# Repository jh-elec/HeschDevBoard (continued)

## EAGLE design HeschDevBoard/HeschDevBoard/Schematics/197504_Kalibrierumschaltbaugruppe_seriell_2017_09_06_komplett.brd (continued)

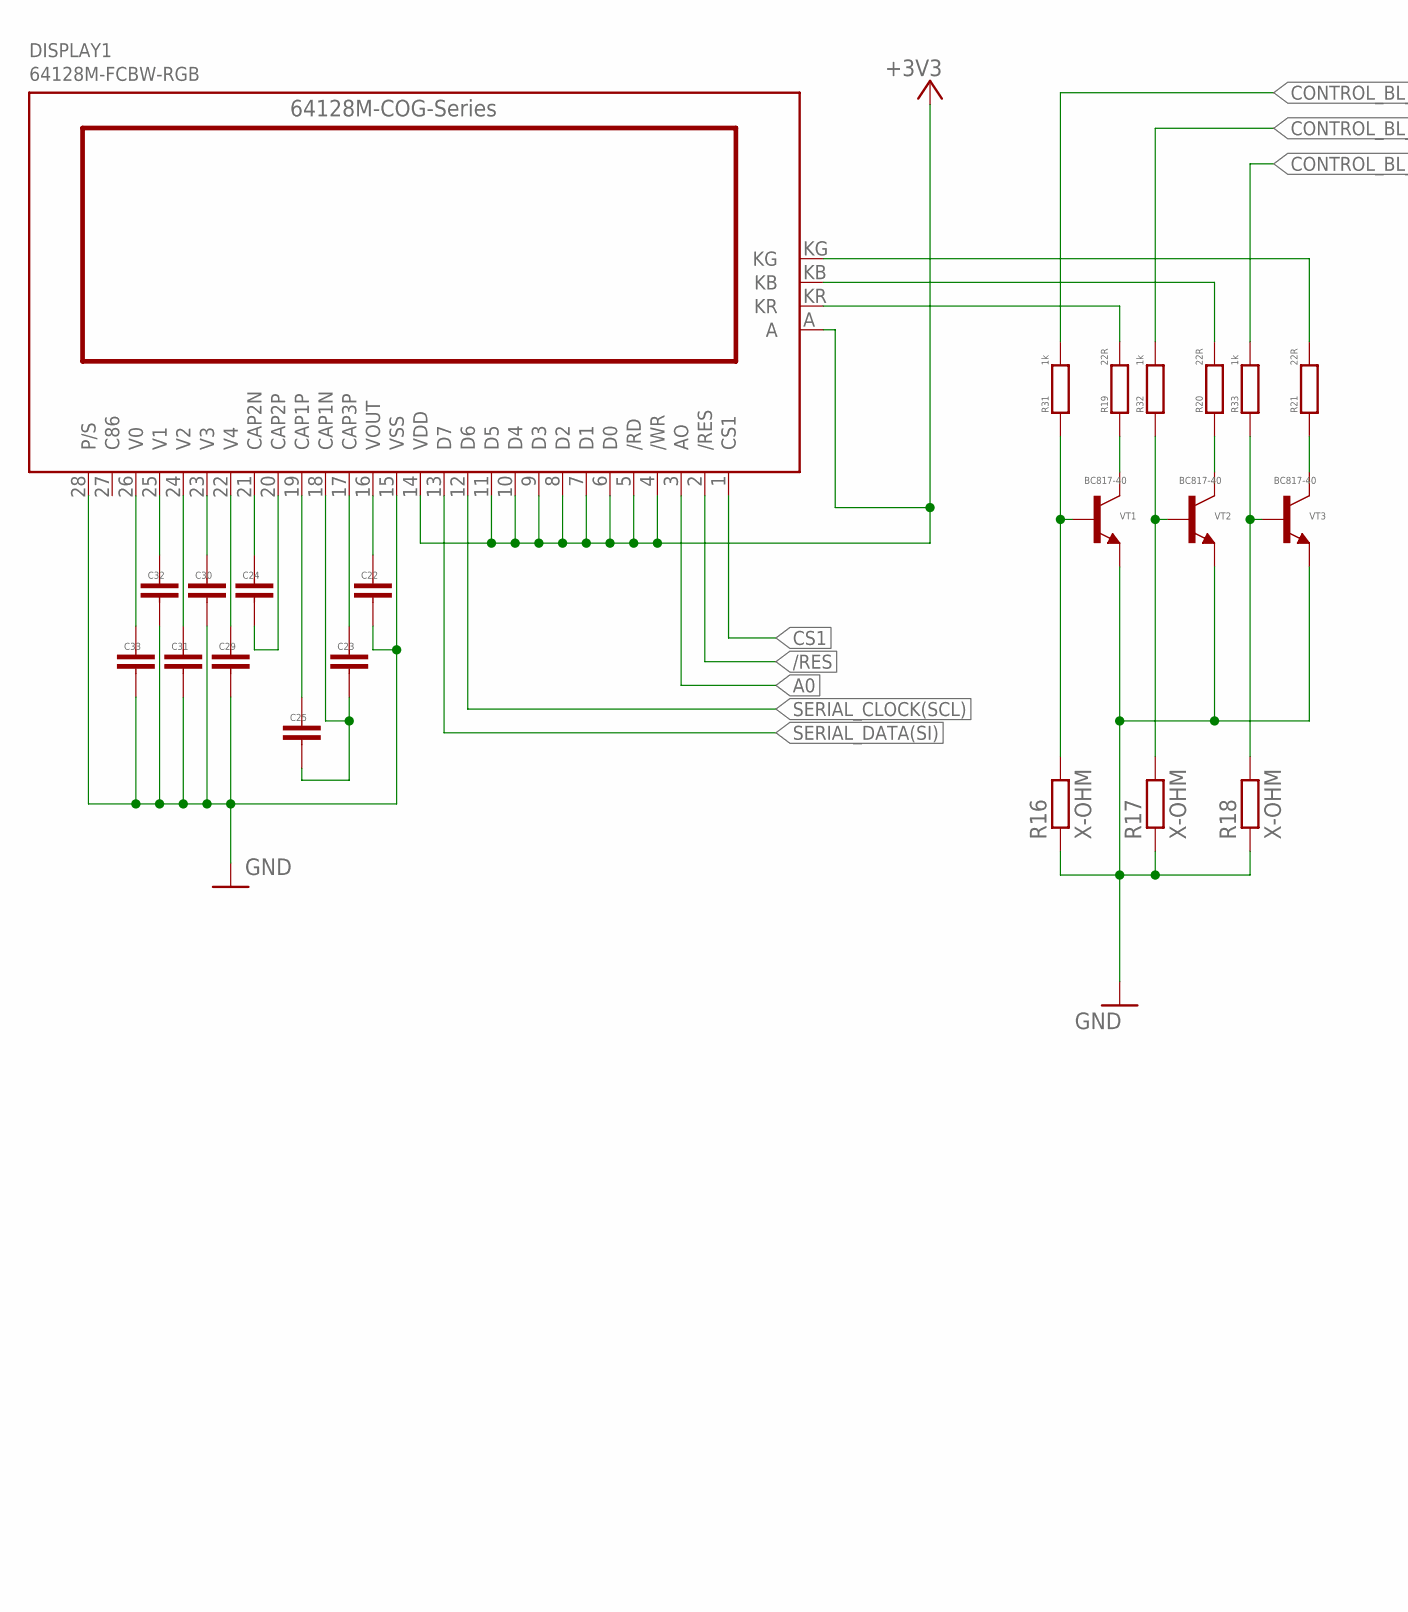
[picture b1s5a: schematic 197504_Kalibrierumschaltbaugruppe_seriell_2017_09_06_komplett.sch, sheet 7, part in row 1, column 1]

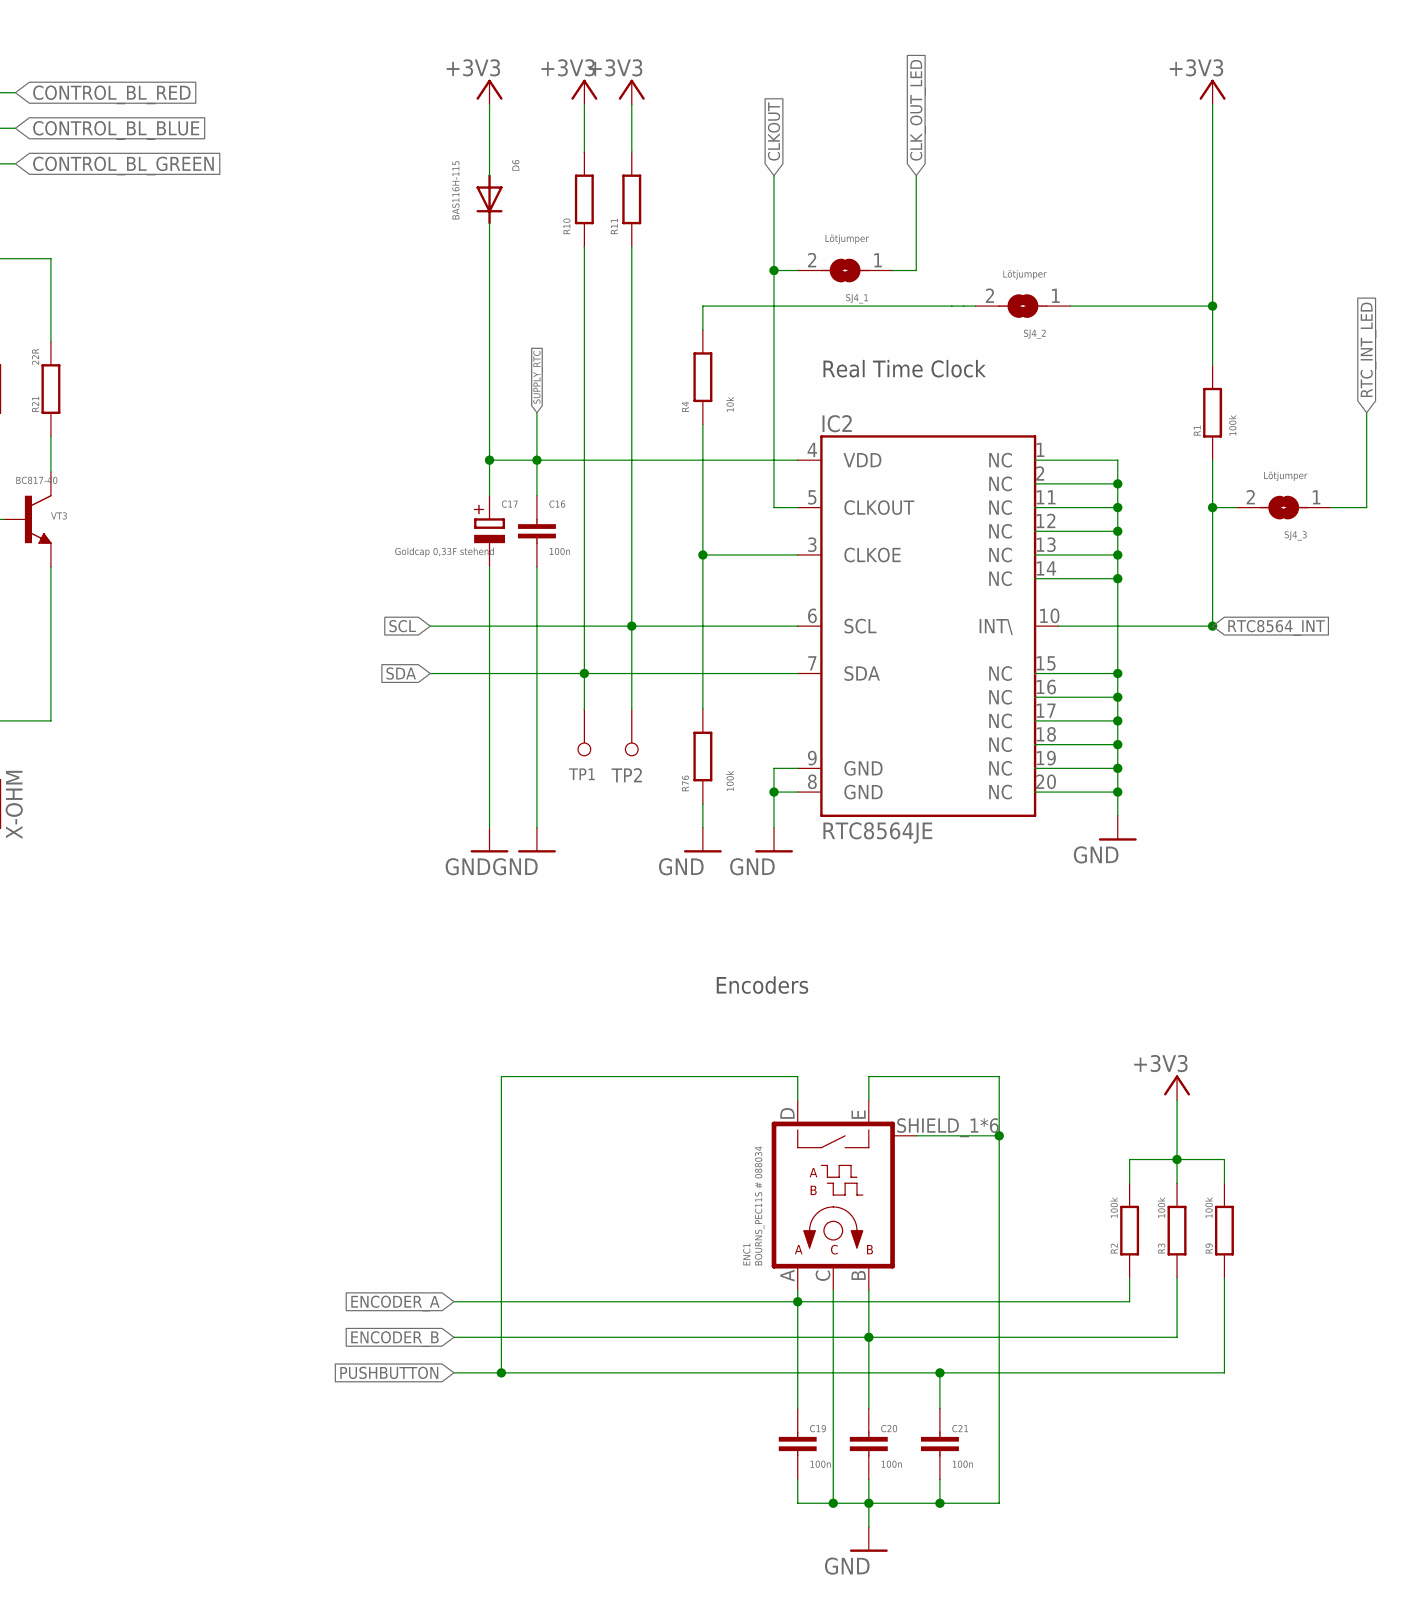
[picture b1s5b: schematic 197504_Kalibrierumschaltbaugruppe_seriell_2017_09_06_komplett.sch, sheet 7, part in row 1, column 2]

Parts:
C16, C19, C20, C21: 100n; C0603
C17: Goldcap 0,33F stehend; PANASONIC_SD_SERIES_STEHEND
C22, C23, C24, C25, C29, C30, C31, C32, C33: 1µ / X7R / 25V mind.; C0603
D6: BAS116H-115; SOD123
DISPLAY1: 64128M-FCBW-RGB; DISPLAYTECH_64128M-FCBW-RGB_COG_SERIES_GLCD-128X68COG
ENC1: BOURNS_PEC11S # 088034; BOURNS_PEC11S
IC2: EPSON RTC8564JE; VSOJ20
R1, R2, R3, R9, R76: 100k; R0603
R4: 10k; R0603
R10, R11: 4,7k; R0603
R16, R17, R18: X-OHM; R0603
R19, R20, R21: 22R; R1206
R31, R32, R33: 1k; R0603
SJ4_1, SJ4_2, SJ4_3: Lötjumper; SJ
TP1, TP2: Testpad_mit_Bohrung; THT-1X2,54
VT1, VT2, VT3: BC817-40; SOT23-BEC

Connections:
+3V3: D6.A, DISPLAY1.4 (/WR), DISPLAY1.5 (/RD), DISPLAY1.6 (D0), DISPLAY1.7 (D1), DISPLAY1.8 (D2), DISPLAY1.9 (D3), DISPLAY1.10 (D4), DISPLAY1.11 (D5), DISPLAY1.14 (VDD), DISPLAY1.A, R1.2, R2.2, R3.2, R9.2, R10.2, R11.2, SJ4_2.1; also elsewhere on the board
/RES: DISPLAY1.2 (/RES); also elsewhere on the board
A0: DISPLAY1.3 (AO); also elsewhere on the board
CLKOUT: IC2.5 (CLKOUT), SJ4_1.2
CLK_OUT_LED: SJ4_1.1; also elsewhere on the board
CONTROL_BL_BLUE: R32.2; also elsewhere on the board
CONTROL_BL_GREEN: R33.2; also elsewhere on the board
CONTROL_BL_RED: R31.2; also elsewhere on the board
CS1: DISPLAY1.1 (CS1); also elsewhere on the board
ENCODER_A: C19.1, ENC1.A, R2.1; also elsewhere on the board
ENCODER_B: C20.1, ENC1.B, R3.1; also elsewhere on the board
GND: C16.2, C17.-, C19.2, C20.2, C21.2, C22.1, C29.1, C30.1, C31.1, C32.1, C33.1, DISPLAY1.15 (VSS), DISPLAY1.28 (P/S), ENC1.C, ENC1.E, ENC1.SHIELD_1, ENC1.SHIELD_2 (SHIELD_1), ENC1.SHIELD_3 (SHIELD_1), ENC1.SHIELD_4 (SHIELD_1), ENC1.SHIELD_5 (SHIELD_1), ENC1.SHIELD_6 (SHIELD_1), IC2.1 (NC), IC2.2 (NC), IC2.8 (GND), IC2.9 (GND), IC2.11 (NC), IC2.12 (NC), IC2.13 (NC), IC2.14 (NC), IC2.15 (NC), IC2.16 (NC), IC2.17 (NC), IC2.18 (NC), IC2.19 (NC), IC2.20 (NC), R16.1, R17.1, R18.1, R76.1, VT1.E, VT2.E, VT3.E; also elsewhere on the board
unnamed: IC2.3 (CLKOE), R4.1, R76.2
unnamed: C22.2, DISPLAY1.16 (VOUT)
unnamed: R16.2, R31.1, VT1.B
unnamed: R17.2, R32.1, VT2.B
unnamed: R4.2, SJ4_2.2
unnamed: R18.2, R33.1, VT3.B
unnamed: DISPLAY1.KG, R21.2
unnamed: C23.2, DISPLAY1.17 (CAP3P)
unnamed: C23.1, C25.1, DISPLAY1.18 (CAP1N)
unnamed: C25.2, DISPLAY1.19 (CAP1P)
unnamed: DISPLAY1.KB, R20.2
unnamed: C24.2, DISPLAY1.21 (CAP2N)
unnamed: C24.1, DISPLAY1.20 (CAP2P)
unnamed: C29.2, DISPLAY1.22 (V4)
unnamed: C30.2, DISPLAY1.23 (V3)
unnamed: C31.2, DISPLAY1.24 (V2)
unnamed: C32.2, DISPLAY1.25 (V1)
unnamed: C33.2, DISPLAY1.26 (V0)
unnamed: DISPLAY1.KR, R19.2
unnamed: R20.1, VT2.C
unnamed: R21.1, VT3.C
unnamed: R19.1, VT1.C
PUSHBUTTON: C21.1, ENC1.D, R9.1; also elsewhere on the board
RTC8564_INT: IC2.10 (INT\), R1.1, SJ4_3.2
RTC_INT_LED: SJ4_3.1; also elsewhere on the board
SCL: IC2.6 (SCL), R11.1, TP2.TP; also elsewhere on the board
SDA: IC2.7 (SDA), R10.1, TP1.TP; also elsewhere on the board
SERIAL_CLOCK(SCL): DISPLAY1.12 (D6); also elsewhere on the board
SERIAL_DATA(SI): DISPLAY1.13 (D7); also elsewhere on the board
SUPPLY_RTC: C16.1, C17.+, D6.C, IC2.4 (VDD)

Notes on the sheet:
Real Time Clock
Encoders

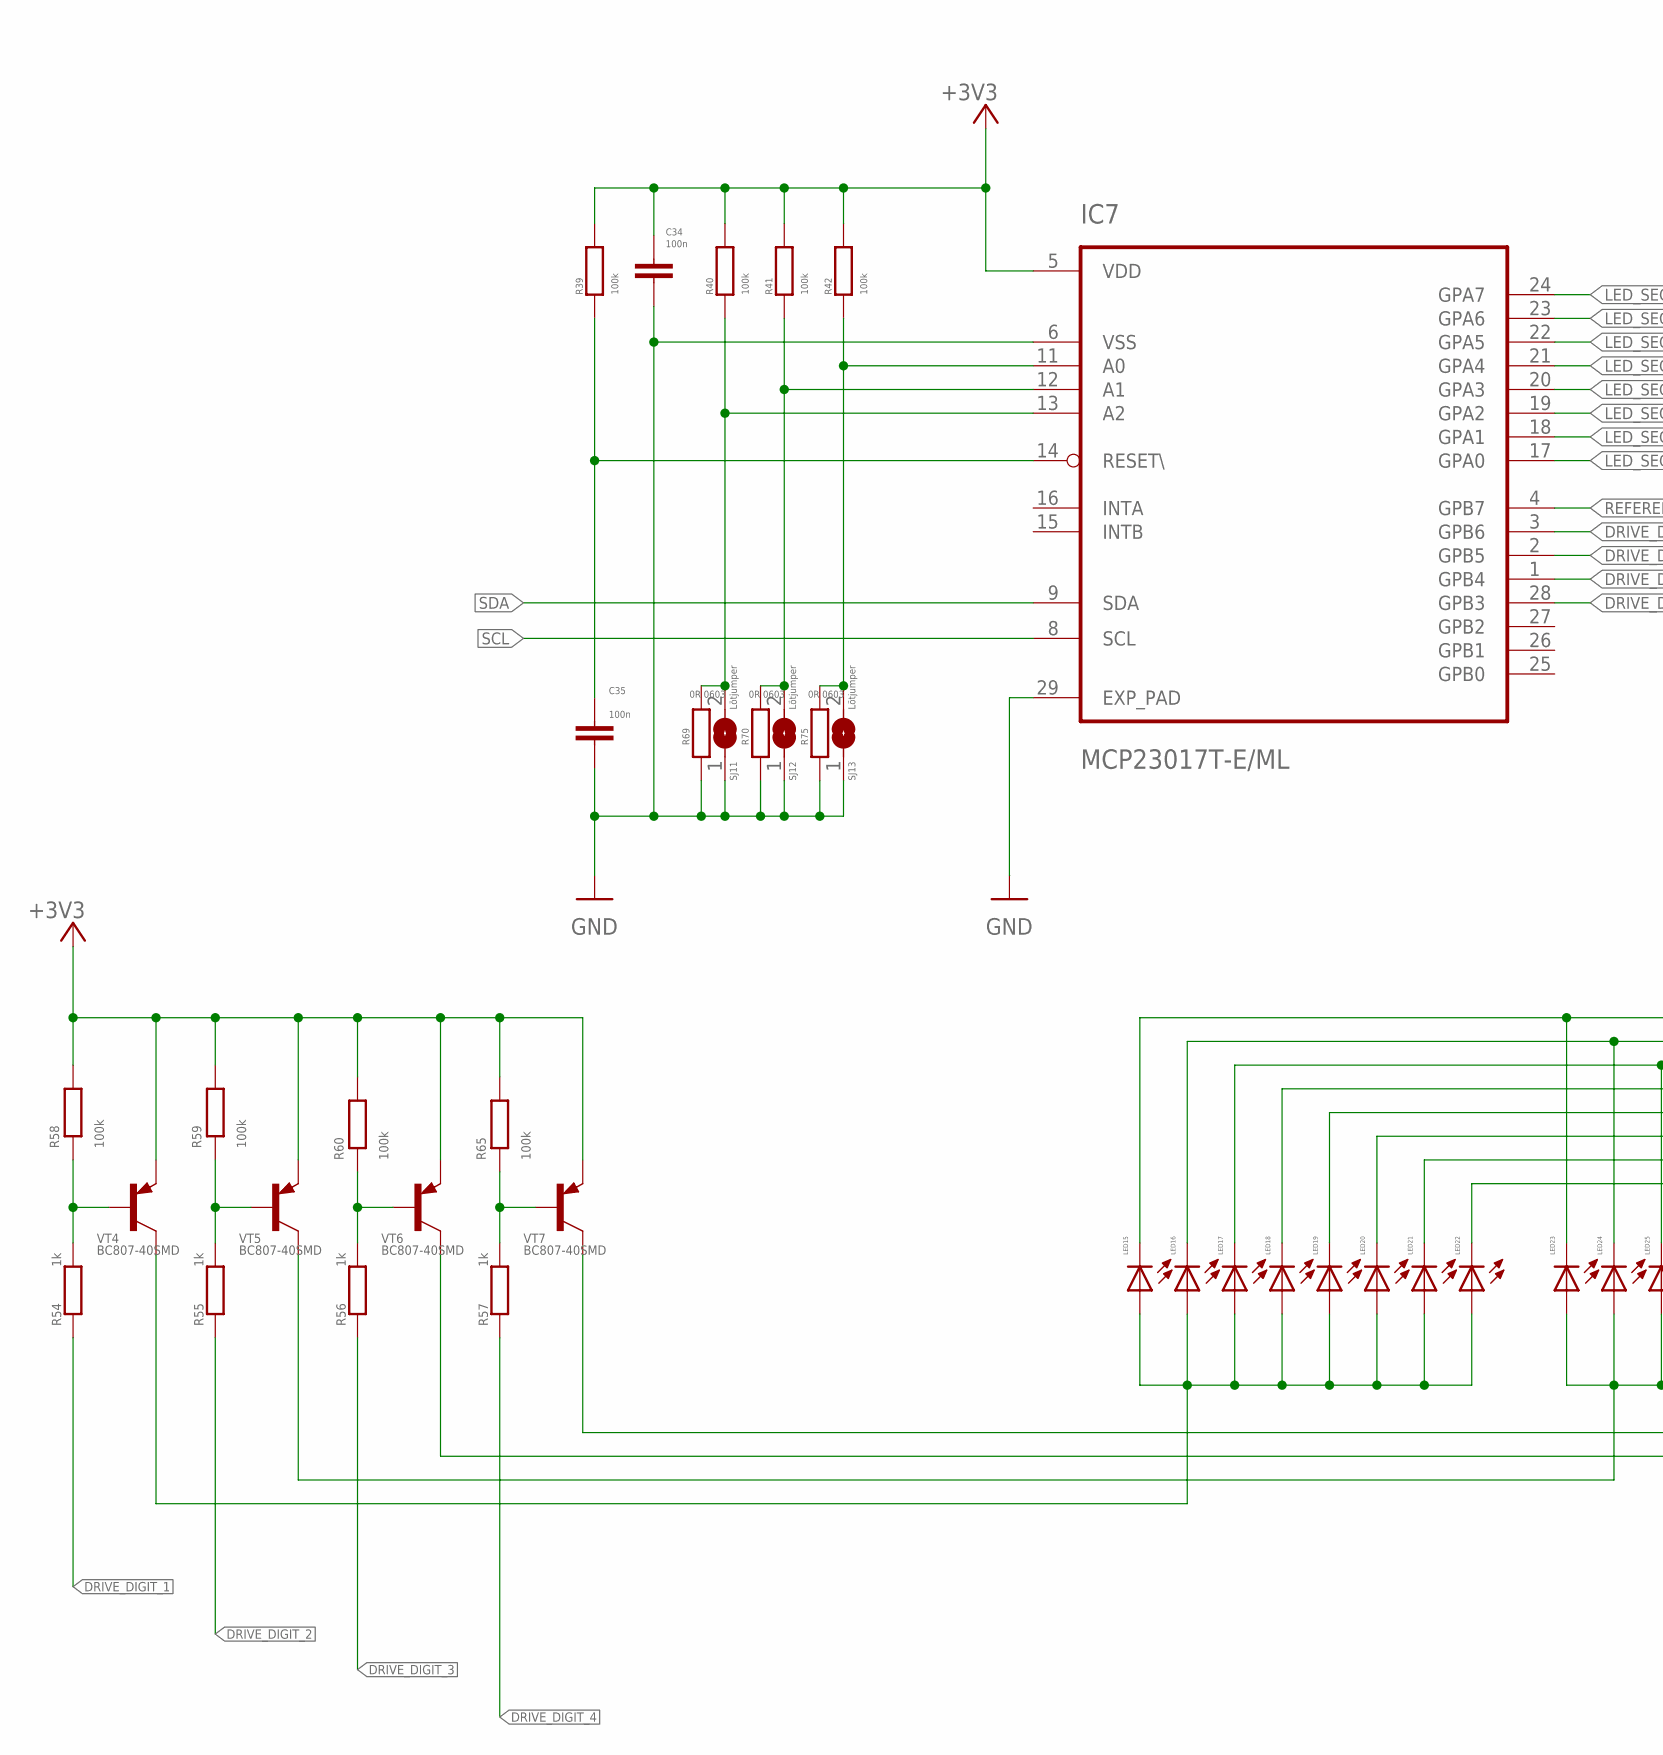
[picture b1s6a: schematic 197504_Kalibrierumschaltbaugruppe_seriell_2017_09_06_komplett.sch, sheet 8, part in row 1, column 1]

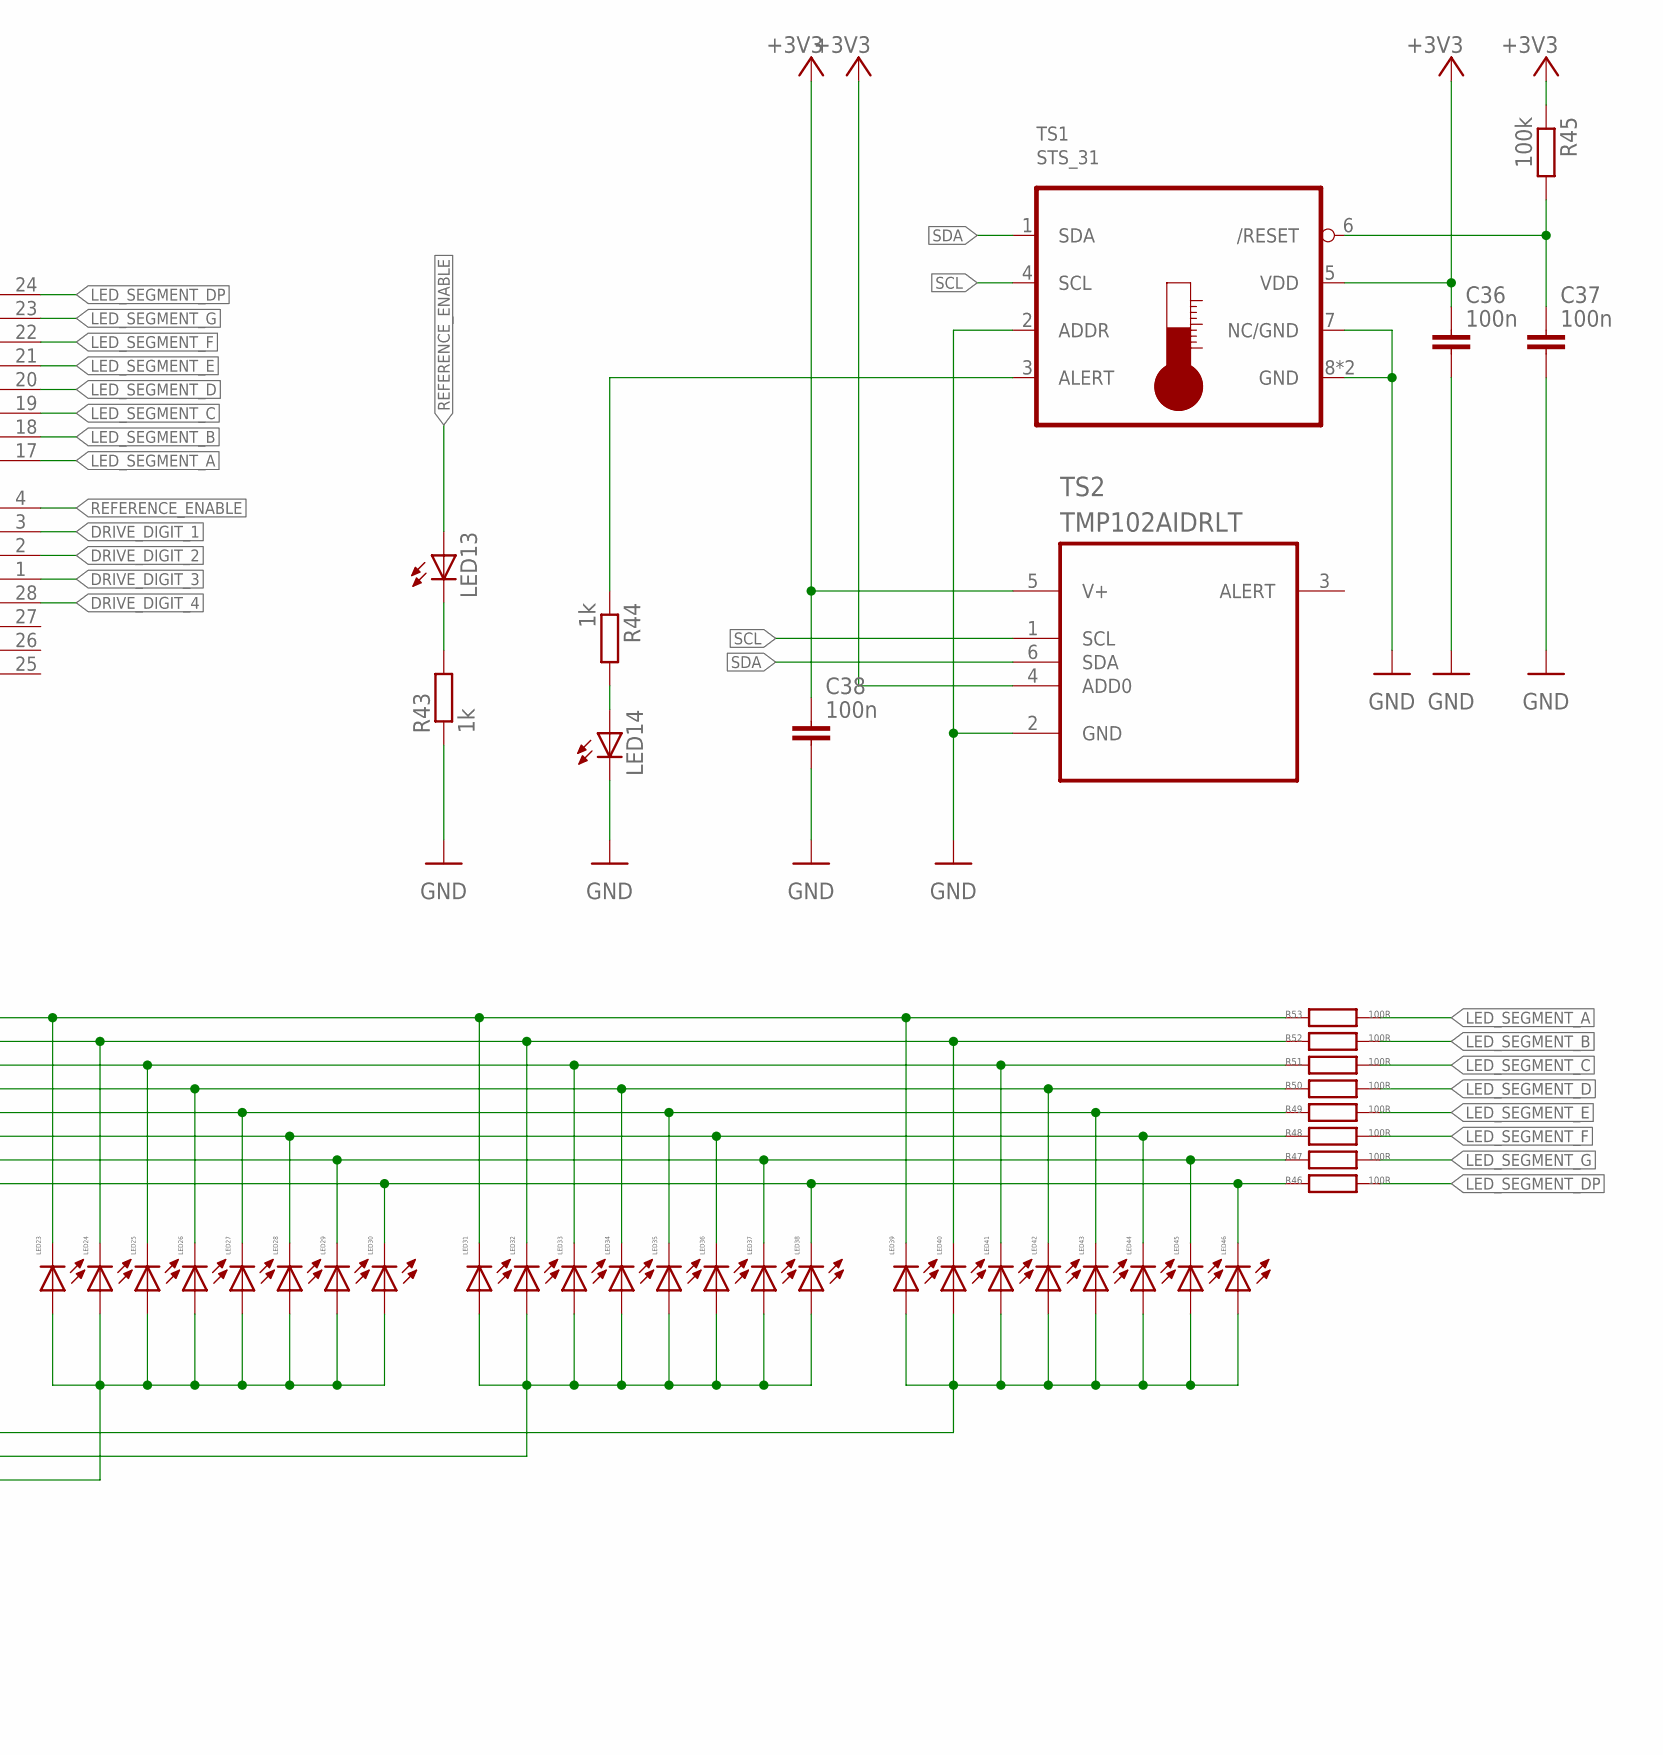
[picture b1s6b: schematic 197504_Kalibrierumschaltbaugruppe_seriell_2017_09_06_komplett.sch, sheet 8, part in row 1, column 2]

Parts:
C34, C35, C36, C37, C38: 100n; C0603
IC7: MCP23017T-E/ML; QFN28_RM_0,65
LED13, LED14: 0805_blue; CHIPLED_0805
LED15, LED16, LED17, LED18, LED19, LED20, LED21, LED22, LED23, LED24, LED25, LED26, LED27, LED28, LED29, LED30, LED31, LED32, LED33, LED34, LED35, LED36, LED37, LED38, LED39, LED40, LED41, LED42, LED43, LED44, LED45, LED46: LED_0603; CHIPLED_0603
R39, R40, R41, R42, R45, R58, R59, R60, R65: 100k; R0603
R43, R44, R54, R55, R56, R57: 1k; R0603
R46, R47, R48, R49, R50, R51, R52, R53: 100R; R0805
R69, R70, R75: 0R 0603; R0603
SJ11, SJ12, SJ13: Lötjumper; SJ
TS1: STS_31; DFN8
TS2: TMP102AIDRLT; SOT50P160X60-6N
VT4, VT5, VT6, VT7: BC807-40SMD; SOT23-BEC

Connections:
+3V3: C34.1, C36.1, C38.1, IC7.5 (VDD), R39.2, R40.2, R41.2, R42.2, R45.1, R58.2, R59.2, R60.2, R65.2, TS1.5 (VDD), TS2.4 (ADD0), TS2.5 (V+), VT4.E, VT5.E, VT6.E, VT7.E; also elsewhere on the board
ANODES_SEGMENT_1: LED15.A, LED16.A, LED17.A, LED18.A, LED19.A, LED20.A, LED21.A, LED22.A, VT4.C
ANODES_SEGMENT_2: LED23.A, LED24.A, LED25.A, LED26.A, LED27.A, LED28.A, LED29.A, LED30.A, VT5.C
ANODES_SEGMENT_3: LED31.A, LED32.A, LED33.A, LED34.A, LED35.A, LED36.A, LED37.A, LED38.A, VT6.C
ANODES_SEGMENT_4: LED39.A, LED40.A, LED41.A, LED42.A, LED43.A, LED44.A, LED45.A, LED46.A, VT7.C
DRIVE_DIGIT_1: IC7.3 (GPB6), R54.1
DRIVE_DIGIT_2: IC7.2 (GPB5), R55.1
DRIVE_DIGIT_3: IC7.1 (GPB4), R56.1
DRIVE_DIGIT_4: IC7.28 (GPB3), R57.1
GND: C34.2, C35.2, C36.2, C37.2, C38.2, IC7.6 (VSS), IC7.29 (EXP_PAD), LED14.C, R43.1, R69.1, R70.1, R75.1, SJ11.1, SJ12.1, SJ13.1, TS1.2 (ADDR), TS1.7 (NC/GND), TS1.8 (GND), TS1.TH (GND), TS2.2 (GND); also elsewhere on the board
LED_SEGMENT_A: IC7.17 (GPA0), R53.2
LED_SEGMENT_A_: LED15.C, LED23.C, LED31.C, LED39.C, R53.1
LED_SEGMENT_B: IC7.18 (GPA1), R52.2
LED_SEGMENT_B_: LED16.C, LED24.C, LED32.C, LED40.C, R52.1
LED_SEGMENT_C: IC7.19 (GPA2), R51.2
LED_SEGMENT_C_: LED17.C, LED25.C, LED33.C, LED41.C, R51.1
LED_SEGMENT_D: IC7.20 (GPA3), R50.2
LED_SEGMENT_DP: IC7.24 (GPA7), R46.2
LED_SEGMENT_DP_: LED22.C, LED30.C, LED38.C, LED46.C, R46.1
LED_SEGMENT_D_: LED18.C, LED26.C, LED34.C, LED42.C, R50.1
LED_SEGMENT_E: IC7.21 (GPA4), R49.2
LED_SEGMENT_E_: LED19.C, LED27.C, LED35.C, LED43.C, R49.1
LED_SEGMENT_F: IC7.22 (GPA5), R48.2
LED_SEGMENT_F_: LED20.C, LED28.C, LED36.C, LED44.C, R48.1
LED_SEGMENT_G: IC7.23 (GPA6), R47.2
LED_SEGMENT_G_: LED21.C, LED29.C, LED37.C, LED45.C, R47.1
unnamed: LED13.C, R43.2
unnamed: C35.1, IC7.14 (RESET\), R39.1
unnamed: IC7.11 (A0), R42.1, R75.2, SJ13.2
unnamed: IC7.13 (A2), R40.1, R69.2, SJ11.2
unnamed: IC7.12 (A1), R41.1, R70.2, SJ12.2
unnamed: R57.2, R65.1, VT7.B
unnamed: LED14.A, R44.2
unnamed: C37.1, R45.2, TS1.6 (/RESET)
unnamed: R56.2, R60.1, VT6.B
unnamed: R44.1, TS1.3 (ALERT)
unnamed: R55.2, R59.1, VT5.B
unnamed: R54.2, R58.1, VT4.B
REFERENCE_ENABLE: IC7.4 (GPB7), LED13.A; also elsewhere on the board
SCL: IC7.8 (SCL), TS1.4 (SCL), TS2.1 (SCL); also elsewhere on the board
SDA: IC7.9 (SDA), TS1.1 (SDA), TS2.6 (SDA); also elsewhere on the board

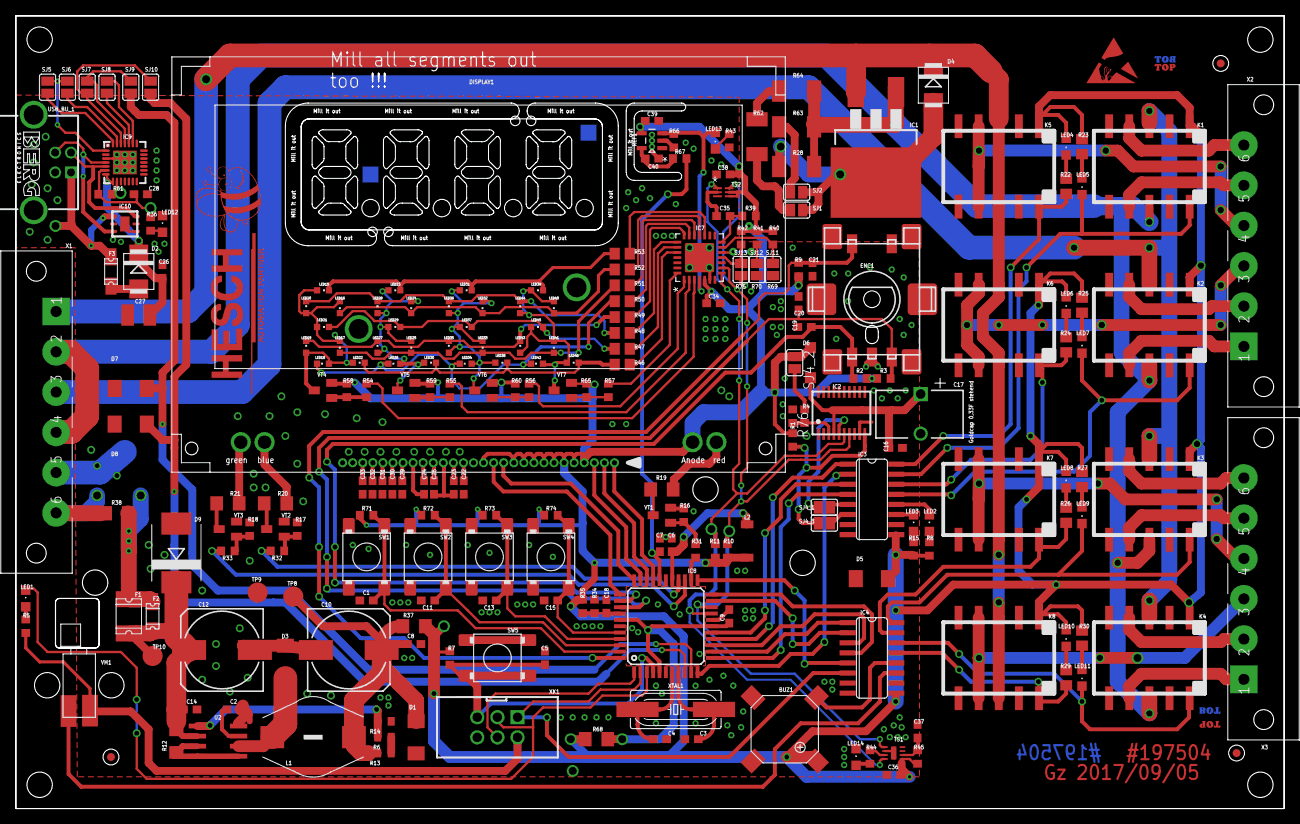
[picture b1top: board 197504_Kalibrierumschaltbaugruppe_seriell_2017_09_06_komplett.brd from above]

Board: 2 copper layers, 160.0 x 100.0 mm, 260 parts (0 on the bottom side), 171 nets.

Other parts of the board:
7_SEG_KONT_1, 7_SEG_KONT_2, 7_SEG_KONT_3, 7_SEG_KONT_4: SIEBEN_SEGMENT_KONTUR_SINGLE_DIGIT
DRILEGEND: DRILEGEND
U$4, U$9: BOT
U$5, U$10: TOP
U$6: HANDHABUNGSVORSCHRIFTEN_BEACHTEN_KOMPLETT_LACKFREI
U$7: HESCH-LOGO-BIENE

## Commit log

2018-07-23 Projekt veröffentlicht
2018-09-25 In der cmd.c das CRC Verfahren angepasst.
